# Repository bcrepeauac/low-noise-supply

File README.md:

# low-noise-supply
Low noise power supply.

# Board URL
<a href="https://oshpark.com/shared_projects/OTFHXp0J"></img></a>

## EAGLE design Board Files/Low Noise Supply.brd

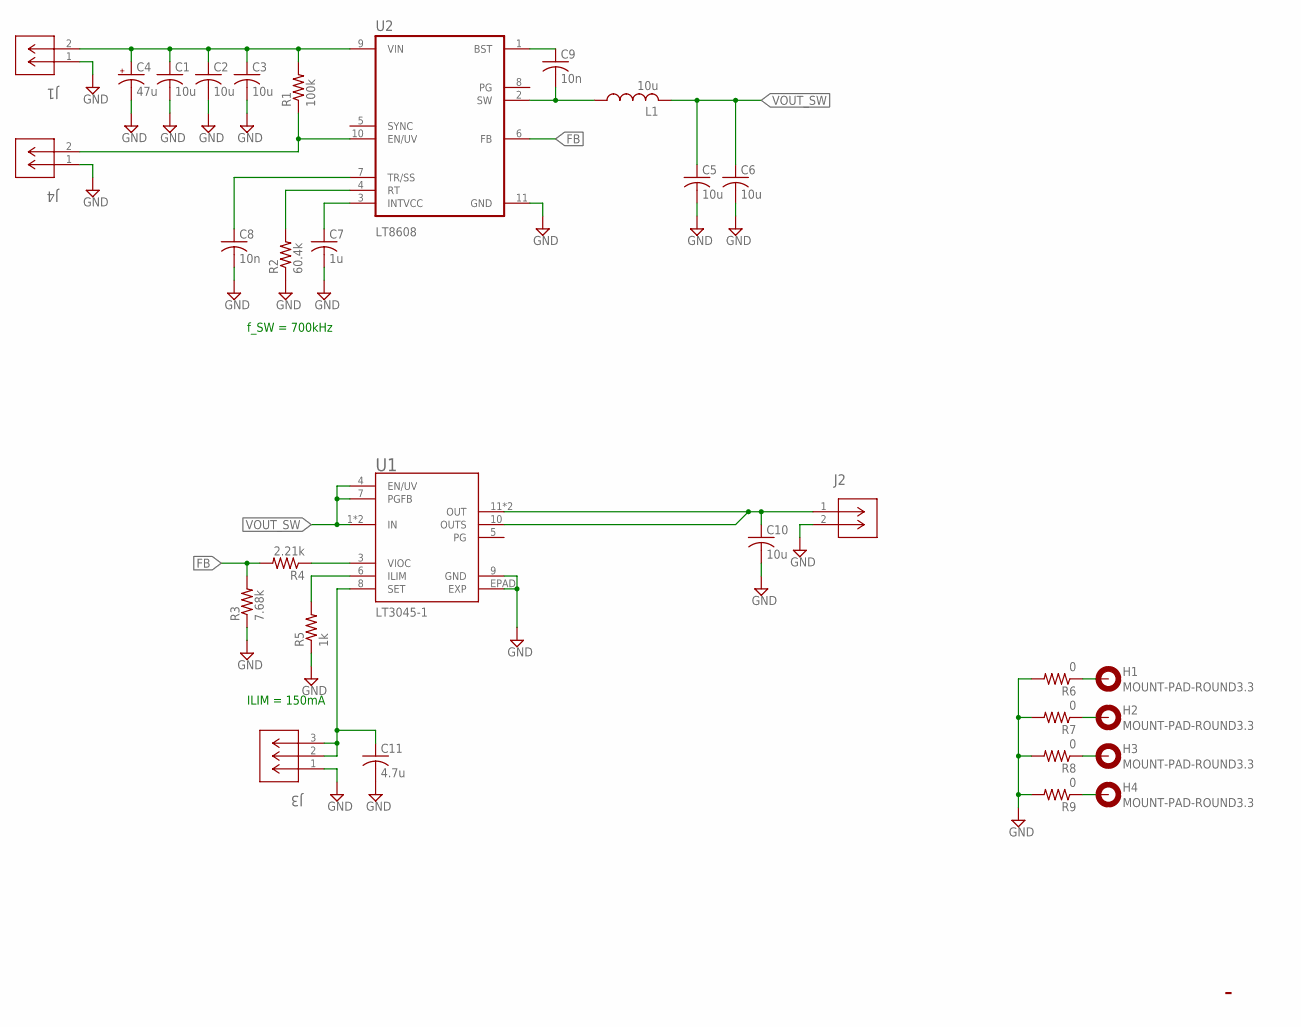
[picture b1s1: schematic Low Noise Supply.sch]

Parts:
C1, C2, C3, C5, C6, C10: 10u; C2220K
C4: 47u; PANASONIC_F
C7: 1u; C0805
C8, C9: 10n; C0805
C11: 4.7u; C0805
H1, H2, H3, H4: MOUNT-PAD-ROUND3.3; 3,3-PAD
J1, J2, J4: OSTVN02A150; CONN_OSTVN02A150_OST
J3: OSTVN03A150; CONN3_OSTVN03A150_OST
L1: 10u; R0805
R1: 100k; R0805
R2: 60.4k; R0805
R3: 7.68k; R0805
R4: 2.21k; R0805
R5: 1k; R0805
R6, R7, R8, R9: 0; R0805
U1: LT3045-1; MSOP12_MSE_ADI-M
U2: LT8608; MSOP-10_MSE

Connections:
FB: R3.2, R4.2, U2.6 (FB)
GND: C1.2, C2.2, C3.2, C4.-, C5.2, C6.2, C7.2, C8.2, C10.2, C11.2, J1.1, J2.2, J3.1, J4.1, R2.1, R3.1, R5.1, R6.2, R7.2, R8.2, R9.2, U1.9 (GND), U1.EPAD (EXP), U2.11 (GND)
unnamed: C1.1, C2.1, C3.1, C4.+, J1.2, R1.2, U2.9 (VIN)
unnamed: J4.2, R1.1, U2.10 (EN/UV)
unnamed: C7.1, U2.3 (INTVCC)
unnamed: C8.1, U2.7 (TR/SS)
unnamed: R2.2, U2.4 (RT)
unnamed: C9.2, L1.1, U2.2 (SW)
unnamed: C9.1, U2.1 (BST)
unnamed: R4.1, U1.3 (VIOC)
unnamed: C10.1, J2.1, U1.10 (OUTS), U1.11 (OUT), U1.12 (OUT)
unnamed: C11.1, J3.2, J3.3, U1.8 (SET)
unnamed: R5.2, U1.6 (ILIM)
unnamed: H1.B3,3, R6.1
unnamed: H2.B3,3, R7.1
unnamed: H3.B3,3, R8.1
unnamed: H4.B3,3, R9.1
VOUT_SW: C5.1, C6.1, L1.2, U1.1 (IN), U1.2 (IN), U1.4 (EN/UV), U1.7 (PGFB)

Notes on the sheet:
f_SW = 700kHz
ILIM = 150mA

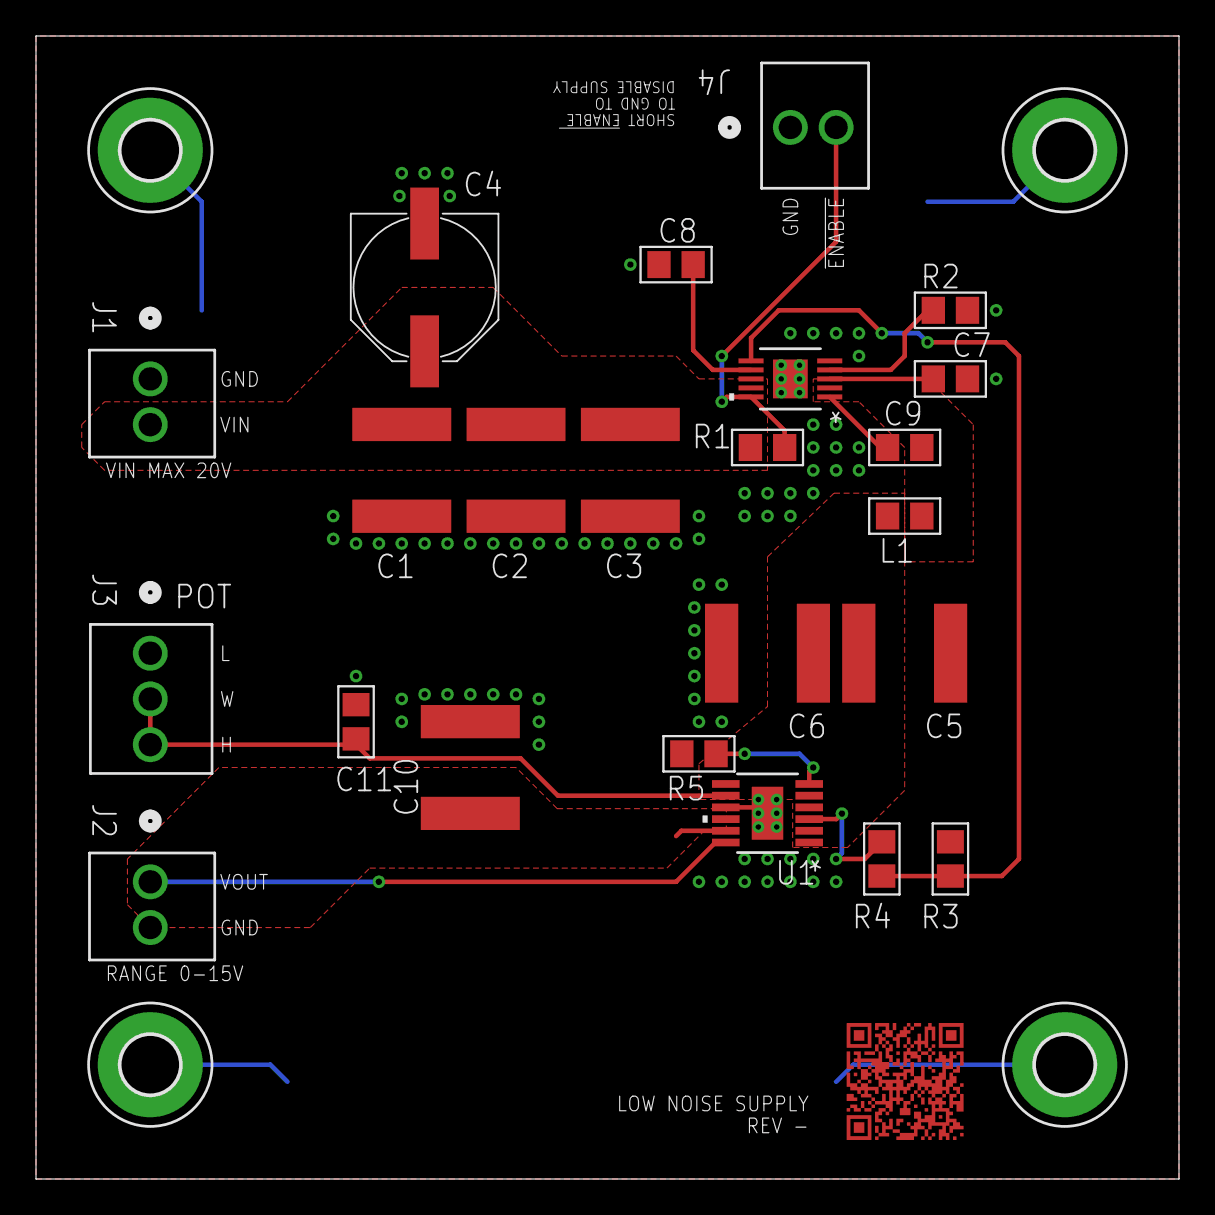
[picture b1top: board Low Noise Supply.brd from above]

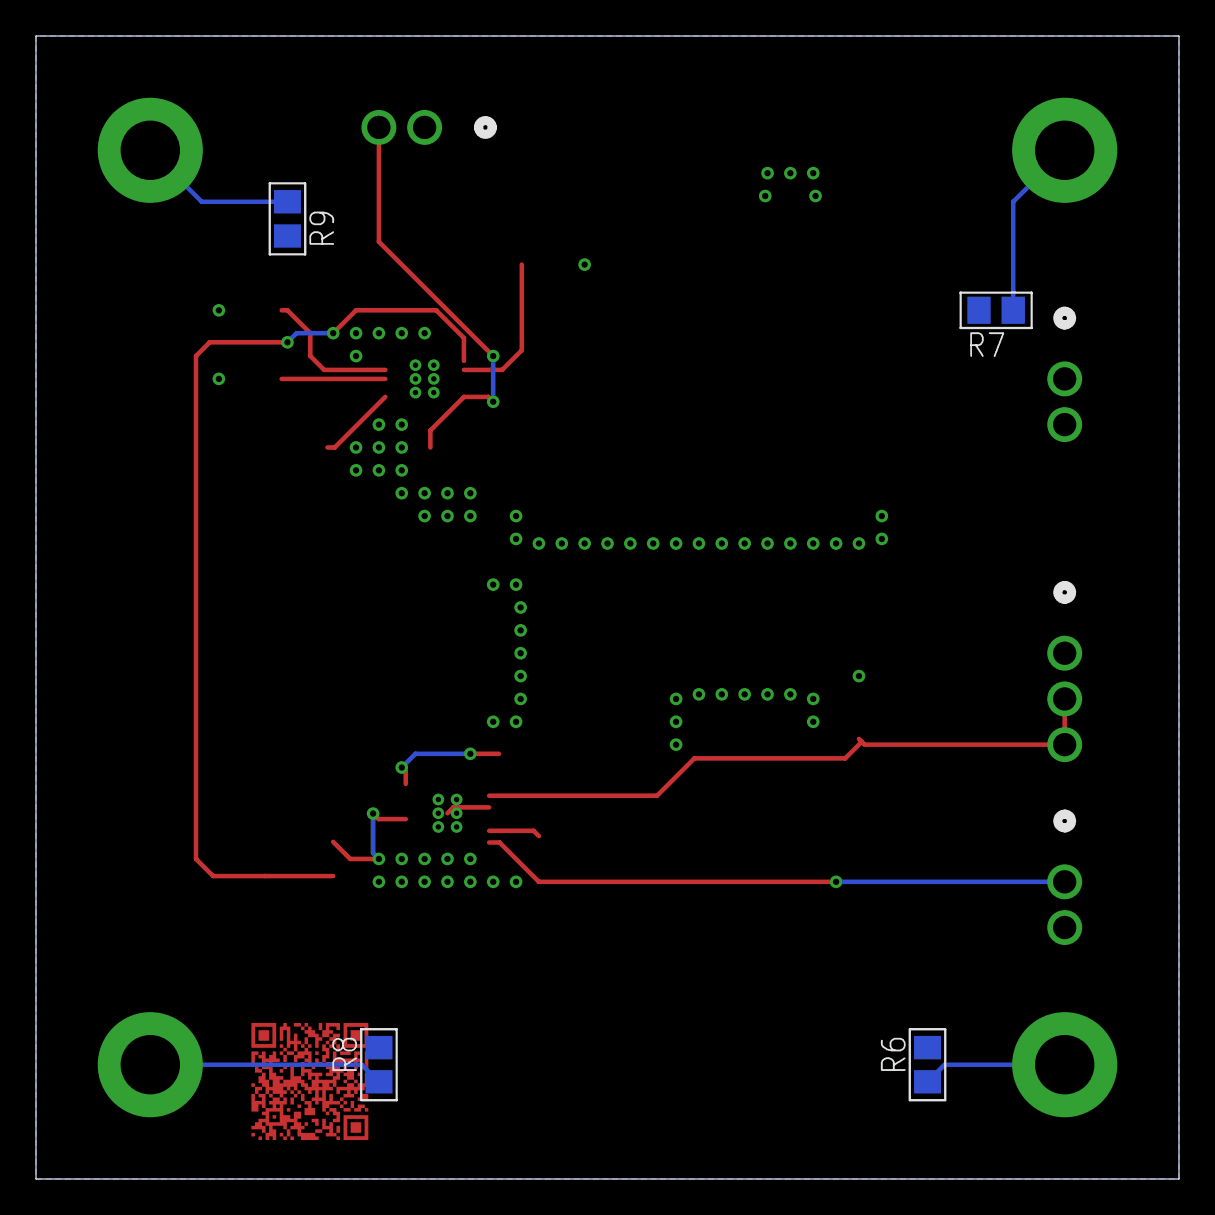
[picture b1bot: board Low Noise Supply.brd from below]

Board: 2 copper layers, 63.5 x 63.5 mm, 31 parts (4 on the bottom side), 18 nets.

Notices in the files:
parts and their libraries:
COPYRIGHT: Copyright (C) 2022 Ultra Librarian. All rights reserved.
COPYRIGHT: Copyright (C) 2023 Ultra Librarian. All rights reserved.
